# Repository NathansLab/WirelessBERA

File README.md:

# Wireless BERA

**Wireless Biopotential Electrode Recording Amplifier**

A wireless, battery-powered biopotential recording system for EEG and auditory
brainstem response (ABR/BERA) measurements.

> **BERA** stands for two things in this project:
> - **B**rainstem **E**voked **R**esponse **A**udiometry — the clinical application
> - **B**iopotential **E**lectrode **R**ecording **A**mplifier — the hardware

> **v1.0** — fabricated at Aisler, assembled, and running. Bring-up status and
> open items: [`docs/hardware_bringup_plan.md`](docs/hardware_bringup_plan.md).

---

## Repository layout

| | |
|---|---|
| [`hardware/`](hardware/) | KiCad 10 project, symbol/footprint library, LTspice simulations, fabrication outputs |
| [`firmware/wireless_bera/`](firmware/wireless_bera/) | ESP-IDF firmware for the ESP32-S3 |
| [`docs/`](docs/) | bring-up status, codec register reference, power architecture, assembly photos |
| [`measurements/`](measurements/) | raw recordings (ECG/DRL, first ABR) and the Python recording/analysis tools |
| [`report/`](report/) | Forschungspraxis report (LaTeX, MFE template) and its PDF |

`hardware/datasheets/` holds the vendor PDFs for every part. It is deliberately
kept out of git — the files are large and always re-downloadable — so a fresh
clone will not have it.

---

## Hardware

**MCU:** ESP32-S3-WROOM-1-N16R8 — Wi-Fi 802.11 b/g/n + Bluetooth 5.0 LE,
16 MB flash, 8 MB octal PSRAM.

**Analog front end**

- **LTC6373** programmable-gain instrumentation amplifier (0.25× … 16×)
- **TAC5212** 24-bit stereo codec — 2 ADC + 2 DAC channels over I²S
- **IM73A135** differential MEMS microphone for stimulus/environment monitoring
- **OPA376** driven-right-leg circuit for active common-mode rejection

**Signal path**

```
 electrode jack J6 ──► LTC6373 (PGIA) ──► TAC5212 IN2  ─┐
 MEMS mic MK1      ─────────────────────► TAC5212 IN1  ─┤ I²S ──► ESP32-S3 ──► Wi-Fi
 stimulus jack J11 ◄── TAC5212 OUT1P/OUT2P ─────────────┘
 DRL feedback      ◄── OPA376 ◄── input common mode
```

**Power** — see [power_architecture.pdf](docs/power_architecture.pdf):

- BQ24074 single-cell Li-Ion charger with power path
- TPS63000 buck-boost → 3.5 V system rail
- TPS65132W dual charge pump → ±5.4 V raw
- TPS7A39 dual ultra-low-noise LDO → ±5 V (instrumentation amplifier, DRL)
- TPS7A94 LDO → 3.3 V analog · TPS7A2033 LDO → 3.3 V digital
- Star topology and LC filters on all analog rails

**Peripherals:** microSD (SDMMC 4-bit), USB-C (USB 2.0 + ESD protection)

**PCB:** 4-layer, split GNDA/GNDD

### Daughterboard

[`hardware/daughterboard/`](hardware/daughterboard/) is an optional plug-in for
standalone LTC6373 evaluation at fixed gain 16. Stacking several of them
parallels the amplifier inputs and reduces equivalent input noise by √n.

---

## Firmware

The firmware lives in [`firmware/wireless_bera/`](firmware/wireless_bera/) — its
[README](firmware/wireless_bera/README.md) has the full picture, including the
HTTP/WebSocket API and the hardware quirks it has to respect.

It brings the analog front end up, streams both ADC channels to a browser over a
WebSocket, drives the DAC stimulus generator, and runs as its own access point
**and** as a client on an existing network at the same time.

```bash
source ~/esp/esp-idf/export.sh
cd firmware/wireless_bera
idf.py set-target esp32s3
idf.py build
```

Flash at **115200** baud — the ESP32-S3's native USB-CDC needs the slower rate
for the auto-reset handshake to line up with the macOS driver, and then no button
presses are required:

```bash
python3 -m esptool --chip esp32s3 -p /dev/cu.usbmodem101 -b 115200 \
  --before default_reset --after hard_reset write_flash \
  --flash_mode dio --flash_freq 80m --flash_size 16MB \
  0x0     build/bootloader/bootloader.bin \
  0x8000  build/partition_table/partition-table.bin \
  0x10000 build/wireless_bera.bin
```

*(To force bootloader mode by hand: hold BOOT (SW3), tap RESET (SW2), release BOOT.)*

On power-up the board raises the access point `WirelessBERA-XXXX`
(password `bera1234`) and serves its UI at <http://192.168.4.1>. The
USB-Serial/JTAG port carries both the log and a command line — type `help`, or
`wifi "My Network" mypassword` to join an existing 2.4 GHz network. Credentials
are stored in NVS only and never end up in this repository.

---

## Simulation

[`hardware/simulation/`](hardware/simulation/) holds the LTspice work behind the
analog design: transient, AC and noise runs, a common-mode/DRL testbench, and PWL
stimulus files with typical BERA waveforms.

---

## Manufacturing

[`hardware/manufacturing/`](hardware/manufacturing/) carries everything the v1.0
build was made from:

- `aisler/` — the Aisler 4-layer design-rule project
- `export/` — Gerbers, STEP models, schematic and PCB prints, BOM and Mouser order files
- `previews/` — fabrication previews and photographs of the assembled board

---

## Tools

- **EDA:** KiCad 10
- **Fabrication:** Aisler, 4-layer
- **Firmware:** ESP-IDF v5.2
- **Hardware audit:** [kicad-happy](https://github.com/aklofas/kicad-happy)

Nathan Scheufele

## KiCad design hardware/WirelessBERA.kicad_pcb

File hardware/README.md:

# Hardware

KiCad 10 project for the Wireless BERA v1.0 board.

## Layout

| | |
|---|---|
| `WirelessBERA.kicad_pro` | open this — the root project |
| `WirelessBERA.kicad_sch` | root sheet; the design is split into three sub-sheets |
| `MCU.kicad_sch` | ESP32-S3-WROOM-1, USB-C, microSD, buttons, status LED |
| `Analog.kicad_sch` | LTC6373 PGIA, TAC5212 codec, OPA376 DRL, MEMS microphone, jacks |
| `Power.kicad_sch` | BQ24074 charger, TPS63000, TPS65132W, TPS7A39/7A94/7A2033 |
| `WirelessBERA.kicad_pcb` | 4-layer layout, split GNDA/GNDD |
| `WirelessBERA.kicad_dru` | Aisler 4-layer design rules |
| `library/` | project symbols, footprints and 3D models |
| `daughterboard/` | separate LTC6373 evaluation board, fixed gain 16 |
| `simulation/` | LTspice work behind the analog design |
| `manufacturing/` | what v1.0 was actually built from |
| `datasheets/` | vendor PDFs — present on disk, deliberately not in git |

## Key reference designators

| | |
|---|---|
| `U7` | ESP32-S3-WROOM-1-N16R8 |
| `U10` | LTC6373 programmable-gain instrumentation amplifier |
| `U11` | TAC5212 codec, I²C address `0x50` |
| `U9` | OPA376 driven-right-leg driver |
| `U5` | TPS65132W dual charge pump, I²C address `0x3E` |
| `MK1` | IM73A135 MEMS microphone |
| `J6` | electrode jack (3.5 mm TRS): tip = DRL, ring = Electrode+, sleeve = Electrode− |
| `J11` | stimulus jack (3.5 mm TRS): tip = OUT2P, ring = OUT1P, sleeve = GNDA |
| `J4` | microSD slot · `J5` USB-C · `J1` battery (JST PH) |
| `J7`–`J10`, `J12`, `J13`, `TP1`–`TP22` | test headers and points |

The authoritative pin map as used by the firmware lives in
[`../firmware/wireless_bera/main/board.h`](../firmware/wireless_bera/main/board.h).

## Assembly state

The populated v1.0 board and what is deliberately left off it are documented in
[`../docs/hardware_bringup_plan.md`](../docs/hardware_bringup_plan.md).

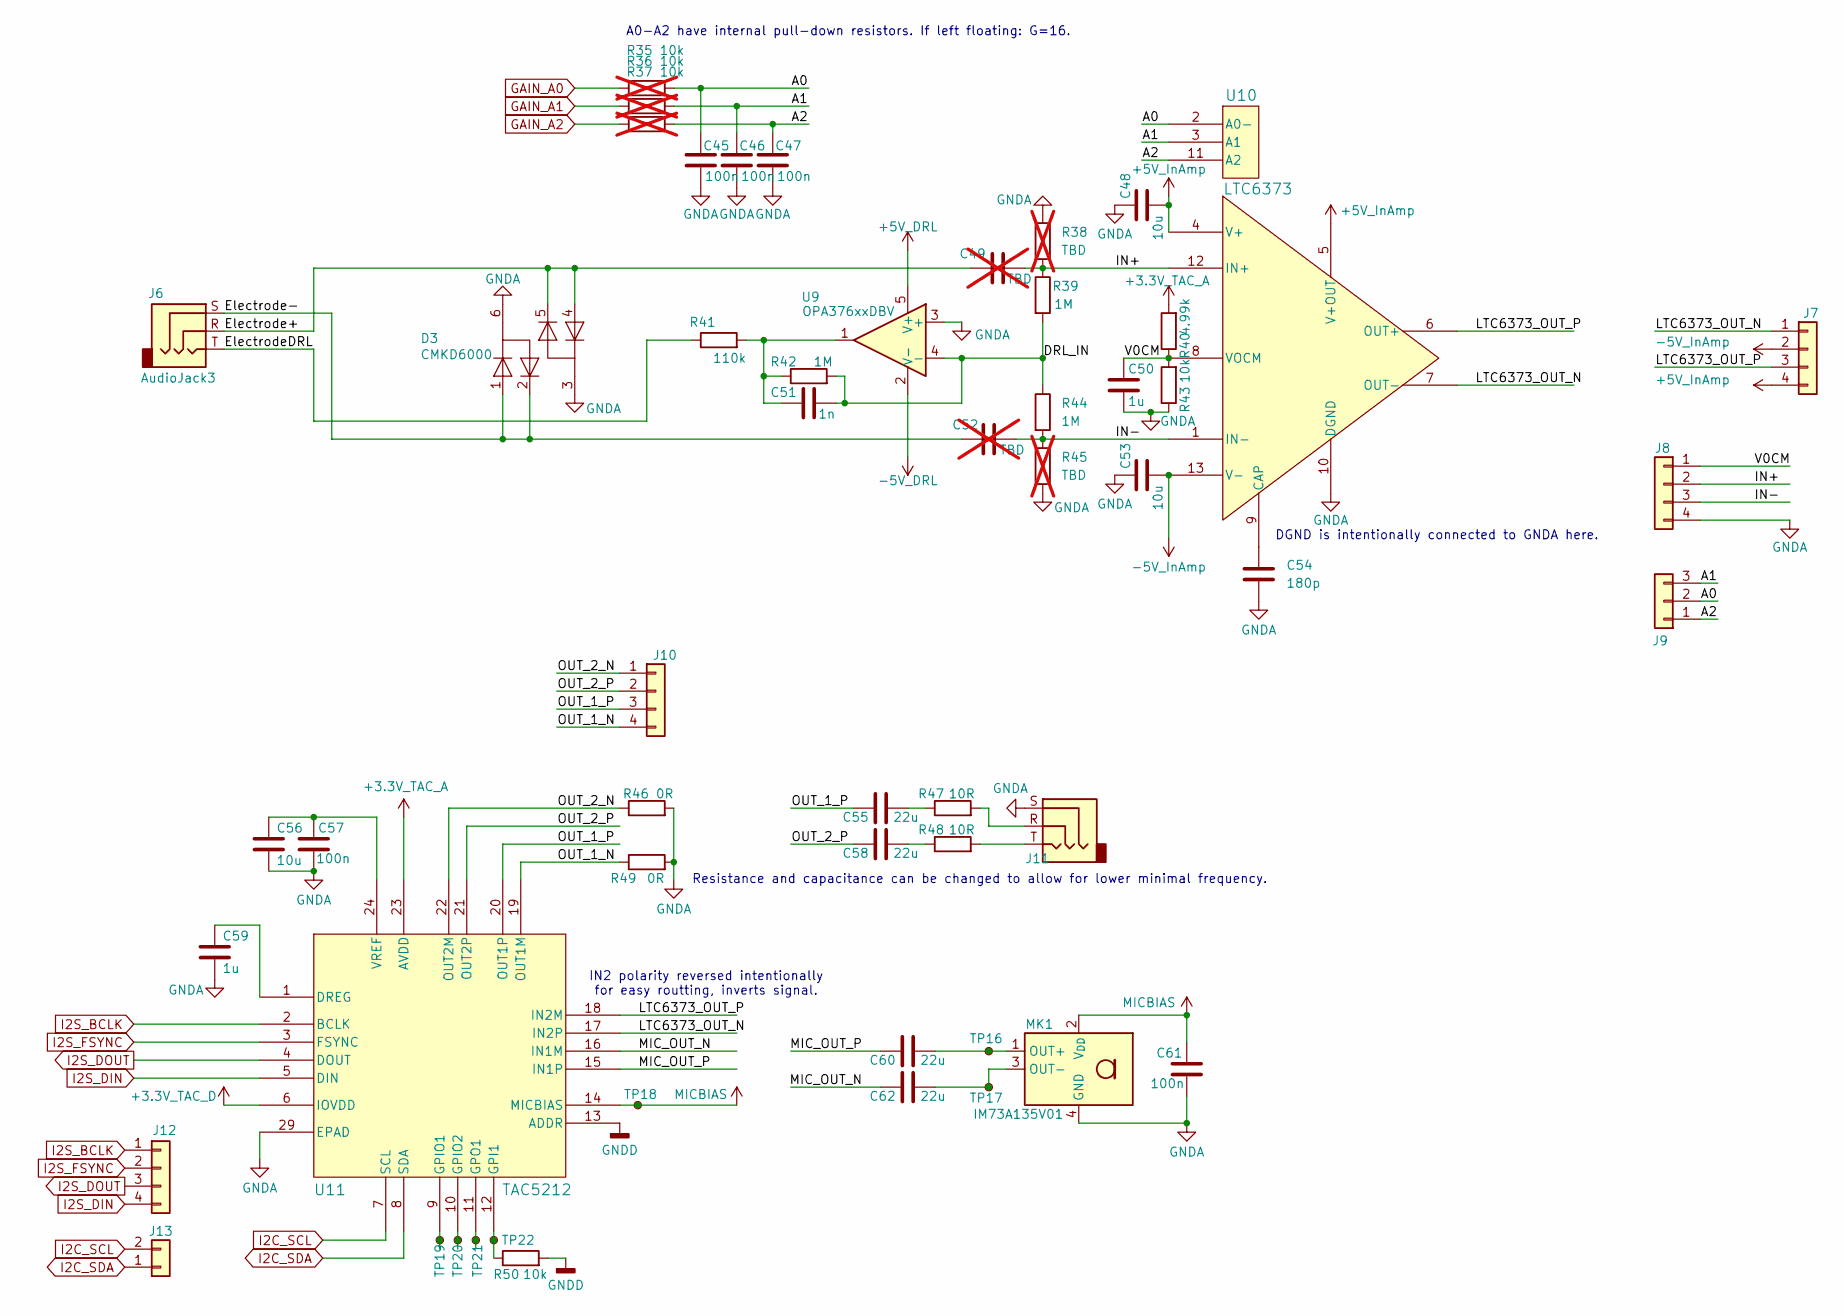
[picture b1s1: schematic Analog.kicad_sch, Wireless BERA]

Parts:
C45, C46, C47, C57, C61: 100n; C_0603_1608Metric; MPN C0603C104K5RACTU
C48, C53: 10u; C_0603_1608Metric; MPN GRM188R61C106MA73J
C49, C52: TBD; C_0603_1608Metric; not fitted
C50, C59: 1u; C_0603_1608Metric; MPN C0603C105K8PACTU
C51: 1n; C_0603_1608Metric; MPN C1608C0G1H102J080AE
C54: 180p; C_0603_1608Metric; MPN C0603C181J5GACTU
C55, C58, C60, C62: 22u; C_0805_2012Metric; MPN GRM21BR60J226ME39L
C56: 10u; C_0805_2012Metric; MPN C0805C106K4PACTU
D3: CMKD6000; SOT-363_SC-70-6; MPN CMKD6000 TR PBFREE
J6, J11: AudioJack3; Jack_3.5mm_CUI_SJ1-3523N_Horizontal; MPN SJ1-3523N
J7, J8, J10, J12: PinHeader_01x04_2.54mm_Vertical; PinHeader_1x04_P2.54mm_Vertical; MPN 61300411121
J9: PinHeader_01x03_2.54mm_Vertical; PinHeader_1x03_P2.54mm_Vertical; MPN 61300311121
J13: PinHeader_01x02_2.54mm_Vertical; PinHeader_1x02_P2.54mm_Vertical; MPN 61300211121
MK1: IM73A135V01; Infineon_PG-LLGA-5-2; MPN IM73A135V01XTSA1
R35, R36, R37: 10k; R_0603_1608Metric; MPN CRCW060310K0FKEA; not fitted
R38, R45: TBD; R_0603_1608Metric; not fitted
R39, R42, R44: 1M; R_0603_1608Metric; MPN CRCW06031M00FKEA
R40: 4.99k; R_0603_1608Metric; MPN CRCW06034K99FKEA
R41: 110k; R_0603_1608Metric; MPN CRCW0603110KFKEA
R43, R50: 10k; R_0603_1608Metric; MPN CRCW060310K0FKEA
R46, R49: 0R; R_0603_1608Metric; MPN CRCW06030000Z0EA
R47, R48: 10R; R_0603_1608Metric; MPN CRCW060310R0FKEA
TP16, TP17, TP18, TP19, TP20, TP21, TP22: TestPoint_Small; TestPoint_Pad_D1.5mm
U9: OPA376xxDBV; SOT-23-5; MPN OPA376AIDBVR
U10: LTC6373; LTC6373_DFN-12; MPN LTC6373IDFM#PBF
U11: TAC5212; TAC5212_VQFN24; MPN TAC5212IRGER

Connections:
+3.3V_TAC_A: R40.2, U11.23 (AVDD); also elsewhere on the board
+3.3V_TAC_D: U11.6 (IOVDD); also elsewhere on the board
+5V_DRL: U9.5 (V+); also elsewhere on the board
+5V_InAmp: C48.2, J7.4, U10.4 (V+), U10.5 (V+OUT); also elsewhere on the board
-5V_DRL: U9.2 (V-); also elsewhere on the board
-5V_InAmp: C53.2, J7.2, U10.13 (V-); also elsewhere on the board
/Analog/A0: C45.1, J9.2, R35.2, U10.2 (A0-)
/Analog/A1: C46.1, J9.3, R36.2, U10.3 (A1)
/Analog/A2: C47.1, J9.1, R37.2, U10.11 (A2)
/Analog/DRL_IN: C51.2, R39.2, R42.2, R44.1, U9.4 (-)
/Analog/Electrode+: C49.1, D3.4, D3.5, J6.R
/Analog/Electrode-: C52.1, D3.1, D3.2, J6.S
/Analog/ElectrodeDRL: J6.T, R41.1
/Analog/IN+: C49.2, J8.2, R38.2, R39.1, U10.12 (IN+)
/Analog/IN-: C52.2, J8.3, R44.2, R45.1, U10.1 (IN-)
/Analog/LTC6373_OUT_N: J7.1, U10.7 (OUT-), U11.17 (IN2P)
/Analog/LTC6373_OUT_P: J7.3, U10.6 (OUT+), U11.18 (IN2M)
/Analog/MIC_OUT_N: C62.1, U11.16 (IN1M)
/Analog/MIC_OUT_P: C60.1, U11.15 (IN1P)
/Analog/OUT_1_N: J10.4, R49.1, U11.19 (OUT1M)
/Analog/OUT_1_P: C55.1, J10.3, U11.20 (OUT1P)
/Analog/OUT_2_N: J10.1, R46.1, U11.22 (OUT2M)
/Analog/OUT_2_P: C58.1, J10.2, U11.21 (OUT2P)
/Analog/V0CM: C50.1, J8.1, R40.1, R43.2, U10.8 (VOCM)
GAIN_A0: R35.1; also elsewhere on the board
GAIN_A1: R36.1; also elsewhere on the board
GAIN_A2: R37.1; also elsewhere on the board
GNDA: C45.2, C46.2, C47.2, C48.1, C50.2, C53.1, C54.2, C56.2, C57.2, C59.2, C61.2, D3.3, D3.6, J8.4, J11.S, MK1.4 (GND), MK1.5 (GND), R38.1, R43.1, R45.2, R46.2, R49.2, U9.3 (+), U10.10 (DGND), U11.29 (EPAD); also elsewhere on the board
GNDD: R50.2, U11.13 (ADDR); also elsewhere on the board
I2C_SCL: J13.2, U11.7 (SCL); also elsewhere on the board
I2C_SDA: J13.1, U11.8 (SDA); also elsewhere on the board
I2S_BCLK: J12.1, U11.2 (BCLK); also elsewhere on the board
I2S_DIN: J12.4, U11.5 (DIN); also elsewhere on the board
I2S_DOUT: J12.3, U11.4 (DOUT); also elsewhere on the board
I2S_FSYNC: J12.2, U11.3 (FSYNC); also elsewhere on the board
MICBIAS: C61.1, MK1.2 (V_{DD}), TP18.1 (1_1), U11.14 (MICBIAS)
unnamed: C51.1, R41.2, R42.1, U9.1
unnamed: C55.2, R47.1
unnamed: C58.2, R48.1
unnamed: J11.R, R47.2
unnamed: J11.T, R48.2
unnamed: C60.2, MK1.1 (OUT+), TP16.1 (1_1)
unnamed: C62.2, MK1.3 (OUT-), TP17.1 (1_1)
unnamed: C54.1, U10.9 (CAP)
unnamed: C59.1, U11.1 (DREG)
unnamed: R50.1, TP22.1 (1_1), U11.12 (GPI1)
unnamed: TP19.1 (1_1), U11.9 (GPIO1)
unnamed: TP20.1 (1_1), U11.10 (GPIO2)
unnamed: TP21.1 (1_1), U11.11 (GPO1)
unnamed: C56.1, C57.1, U11.24 (VREF)

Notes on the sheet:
Resistance and capacitance can be changed to allow for lower minimal frequency.
IN2 polarity reversed intentionally for easy routting, inverts signal.
DGND is intentionally connected to GNDA here.
A0-A2 have internal pull-down resistors. If left floating: G=16.

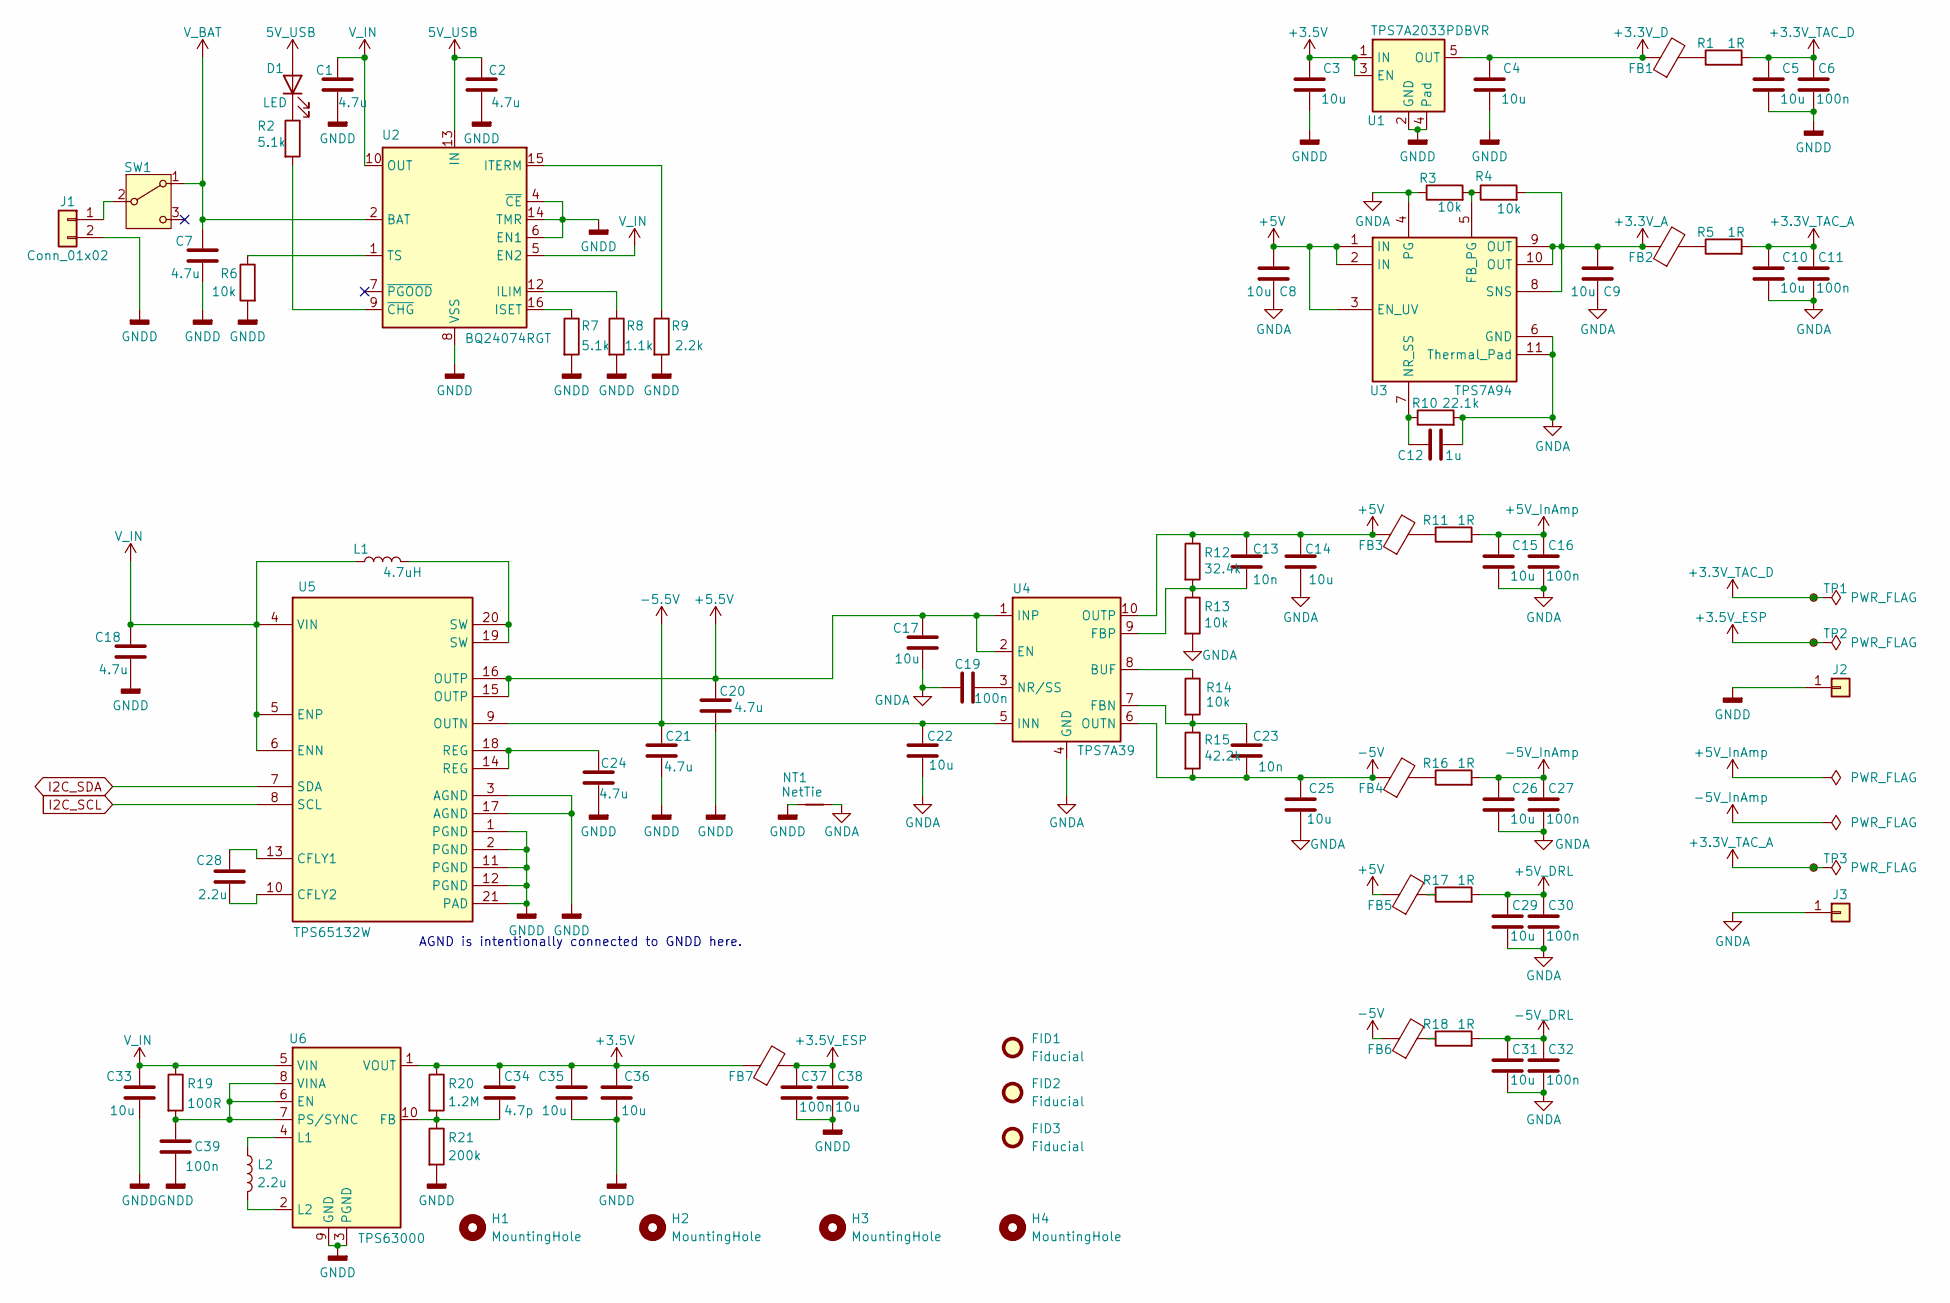
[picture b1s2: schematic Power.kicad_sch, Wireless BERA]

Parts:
C1, C2, C7, C18, C20, C21, C24: 4.7u; C_0805_2012Metric; MPN C0805C475K4PACTU
C3, C4, C5, C8, C9, C10, C14, C15, C17, C22, C25, C26, C29, C31, C33, C35, C36, C38: 10u; C_0805_2012Metric; MPN C0805C106K4PACTU
C6, C11, C16, C19, C27, C30, C32, C37, C39: 100n; C_0603_1608Metric; MPN C0603C104K5RACTU
C12: 1u; C_0603_1608Metric; MPN C0603C105K8PACTU
C13, C23: 10n; C_0603_1608Metric; MPN C0603C103G8GACTU
C28: 2.2u; C_0603_1608Metric; MPN C0603C225K8PACTU
C34: 4.7p; C_0603_1608Metric; MPN C0603C479C4HACTU
D1: LED; LED_0603_1608Metric; MPN 150060VS75000
FB1, FB2, FB3, FB4, FB5, FB6, FB7: FerriteBead; L_0805_2012Metric; MPN 742792040
FID1, FID2, FID3: Fiducial; Fiducial_0.5mm_Mask1mm
H1, H2, H3, H4: MountingHole; MountingHole_2.2mm_M2
J1: Conn_01x02; JST_PH_S2B-PH-SM4-TB_1x02-1MP_P2.00mm_Horizontal; MPN S2B-PH-SM4-TB(LF)(SN)
J2, J3: PinHeader_01x01_2.54mm_Vertical; PinHeader_1x01_P2.54mm_Vertical; MPN 61300111121
L1: 4.7uH; L_1008_2520Metric; MPN 1269AS-H-4R7M=P2
L2: 2.2u; L_0805_2012Metric; MPN LQM21PN2R2NGCD
NT1: NetTie; NetTie-2_SMD_Pad2.0mm
R1, R5, R11, R16, R17, R18: 1R; R_0603_1608Metric; MPN CRCW06031R00FKEA
R2, R7: 5.1k; R_0603_1608Metric; MPN CRCW06035K10FKEA
R3, R4, R6, R13, R14: 10k; R_0603_1608Metric; MPN CRCW060310K0FKEA
R8: 1.1k; R_0603_1608Metric; MPN CRCW06031K10FKEA
R9: 2.2k; R_0603_1608Metric; MPN CRCW06032K20FKEA
R10: 22.1k; R_0603_1608Metric; MPN CRCW060322K1FKEA
R12: 32.4k; R_0603_1608Metric; MPN CRCW060332K4FKEA
R15: 42.2k; R_0603_1608Metric; MPN CRCW060342K2FKEA
R19: 100R; R_0603_1608Metric; MPN CRCW0603100RFKEA
R20: 1.2M; R_0603_1608Metric; MPN CRCW06031M20FKEA
R21: 200k; R_0603_1608Metric; MPN CRCW0603200KFKEA
SW1: SW_SPDT; SW_SPDT_CK_JS102011SAQN; MPN JS102011SAQN
TP1, TP2, TP3: TestPoint_Small; TestPoint_Pad_D1.5mm
U1: TPS7A2033PDBVR; SOT-23-5; MPN TPS7A2033PDBVR
U2: BQ24074RGT; VQFN-16-1EP_3x3mm_P0.5mm_EP1.6x1.6mm; MPN BQ24074RGTR
U3: TPS7A94; TPS7A94_WSON-10; MPN TPS7A9401DSCR
U4: TPS7A39; Texas_S-PVSON-N10_ThermalVias; MPN TPS7A3901DSCR
U5: TPS65132W; TPS65132W_WQFN-20-TI; MPN TPS65132WRVCR
U6: TPS63000; Texas_DRC0010J_ThermalVias; MPN TPS63000DRCR

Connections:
5V_USB: C2.1, D1.2 (A), U2.13 (IN); also elsewhere on the board
+3.3V_A: C9.2, FB2.1, R4.2, U3.8 (SNS), U3.9 (OUT), U3.10 (OUT)
+3.3V_D: C4.1, FB1.1, U1.5 (OUT)
+3.3V_TAC_A: C10.1, C11.1, R5.2, TP3.1 (1_1); also elsewhere on the board
+3.3V_TAC_D: C5.1, C6.1, R1.2, TP1.1 (1_1); also elsewhere on the board
+3.5V: C3.1, C34.1, C35.1, C36.1, FB7.1, R20.1, U1.1 (IN), U1.3 (EN), U6.1 (VOUT)
+3.5V_ESP: C37.1, C38.1, FB7.2, TP2.1 (1_1); also elsewhere on the board
+5.5V: C17.1, C20.1, U4.1 (INP), U4.2 (EN), U5.15 (OUTP), U5.16 (OUTP)
+5V: C8.2, C13.1, C14.1, FB3.1, FB5.1, R12.1, U3.1 (IN), U3.2 (IN), U3.3 (EN_UV), U4.10 (OUTP)
+5V_DRL: C29.1, C30.1, R17.2; also elsewhere on the board
+5V_InAmp: C15.1, C16.1, R11.2; also elsewhere on the board
-5.5V: C21.1, C22.1, U4.5 (INN), U5.9 (OUTN)
-5V: C23.2, C25.1, FB4.1, FB6.1, R15.2, U4.6 (OUTN)
-5V_DRL: C31.1, C32.1, R18.2; also elsewhere on the board
-5V_InAmp: C26.1, C27.1, R16.2; also elsewhere on the board
GNDA: C8.1, C9.1, C10.2, C11.2, C12.2, C14.2, C15.2, C16.2, C17.2, C19.1, C22.2, C25.2, C26.2, C27.2, C29.2, C30.2, C31.2, C32.2, J3.1 (Pin_1_1), NT1.2, R3.1, R10.2, R13.2, U3.4 (PG), U3.6 (GND), U3.11 (Thermal_Pad), U4.4 (GND), U4.11 (GND); also elsewhere on the board
GNDD: C1.2, C2.2, C3.2, C4.2, C5.2, C6.2, C7.2, C18.2, C20.2, C21.2, C24.2, C33.2, C35.2, C36.2, C37.2, C38.2, C39.2, J1.2, J2.1 (Pin_1_1), NT1.1, R6.2, R7.2, R8.2, R9.2, R21.2, U1.2 (GND), U1.4 (Pad), U2.4 (~CE), U2.6 (EN1), U2.8 (VSS), U2.14 (TMR), U2.17 (VSS), U5.1 (PGND), U5.2 (PGND), U5.3 (AGND), U5.11 (PGND), U5.12 (PGND), U5.17 (AGND), U5.21 (PAD), U6.3 (PGND), U6.9 (GND), U6.11 (PGND); also elsewhere on the board
I2C_SCL: U5.8 (SCL); also elsewhere on the board
I2C_SDA: U5.7 (SDA); also elsewhere on the board
unnamed: C24.1, U5.14 (REG), U5.18 (REG)
unnamed: D1.1 (K), R2.1
unnamed: FB1.2, R1.1
unnamed: FB2.2, R5.1
unnamed: FB3.2, R11.1
unnamed: FB4.2, R16.1
unnamed: FB5.2, R17.1
unnamed: FB6.2, R18.1
unnamed: J1.1, SW1.2 (B)
unnamed: L1.2, U5.19 (SW), U5.20 (SW)
unnamed: R8.1, U2.12 (ILIM)
unnamed: R7.1, U2.16 (ISET)
unnamed: R9.1, U2.15 (ITERM)
unnamed: R6.1, U2.1 (TS)
unnamed: R2.2, U2.9 (~CHG)
unnamed: R3.2, R4.1, U3.5 (FB_PG)
unnamed: C12.1, R10.1, U3.7 (NR_SS)
unnamed: R14.1, U4.8 (BUF)
unnamed: C23.1, R14.2, R15.1, U4.7 (FBN)
unnamed: C13.2, R12.2, R13.1, U4.9 (FBP)
unnamed: C19.2, U4.3 (NR/SS)
unnamed: C28.1, U5.13 (CFLY1)
unnamed: C28.2, U5.10 (CFLY2)
unnamed: C39.1, R19.2, U6.6 (EN), U6.7 (PS/SYNC), U6.8 (VINA)
unnamed: C34.2, R20.2, R21.1, U6.10 (FB)
unnamed: L2.1, U6.4 (L1)
unnamed: L2.2, U6.2 (L2)
V_BAT: C7.1, SW1.1 (A), U2.2 (BAT), U2.3 (BAT); also elsewhere on the board
V_IN: C1.1, C18.1, C33.1, L1.1, R19.1, U2.5 (EN2), U2.10 (OUT), U2.11 (OUT), U5.4 (VIN), U5.5 (ENP), U5.6 (ENN), U6.5 (VIN)

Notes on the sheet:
AGND is intentionally connected to GNDD here.

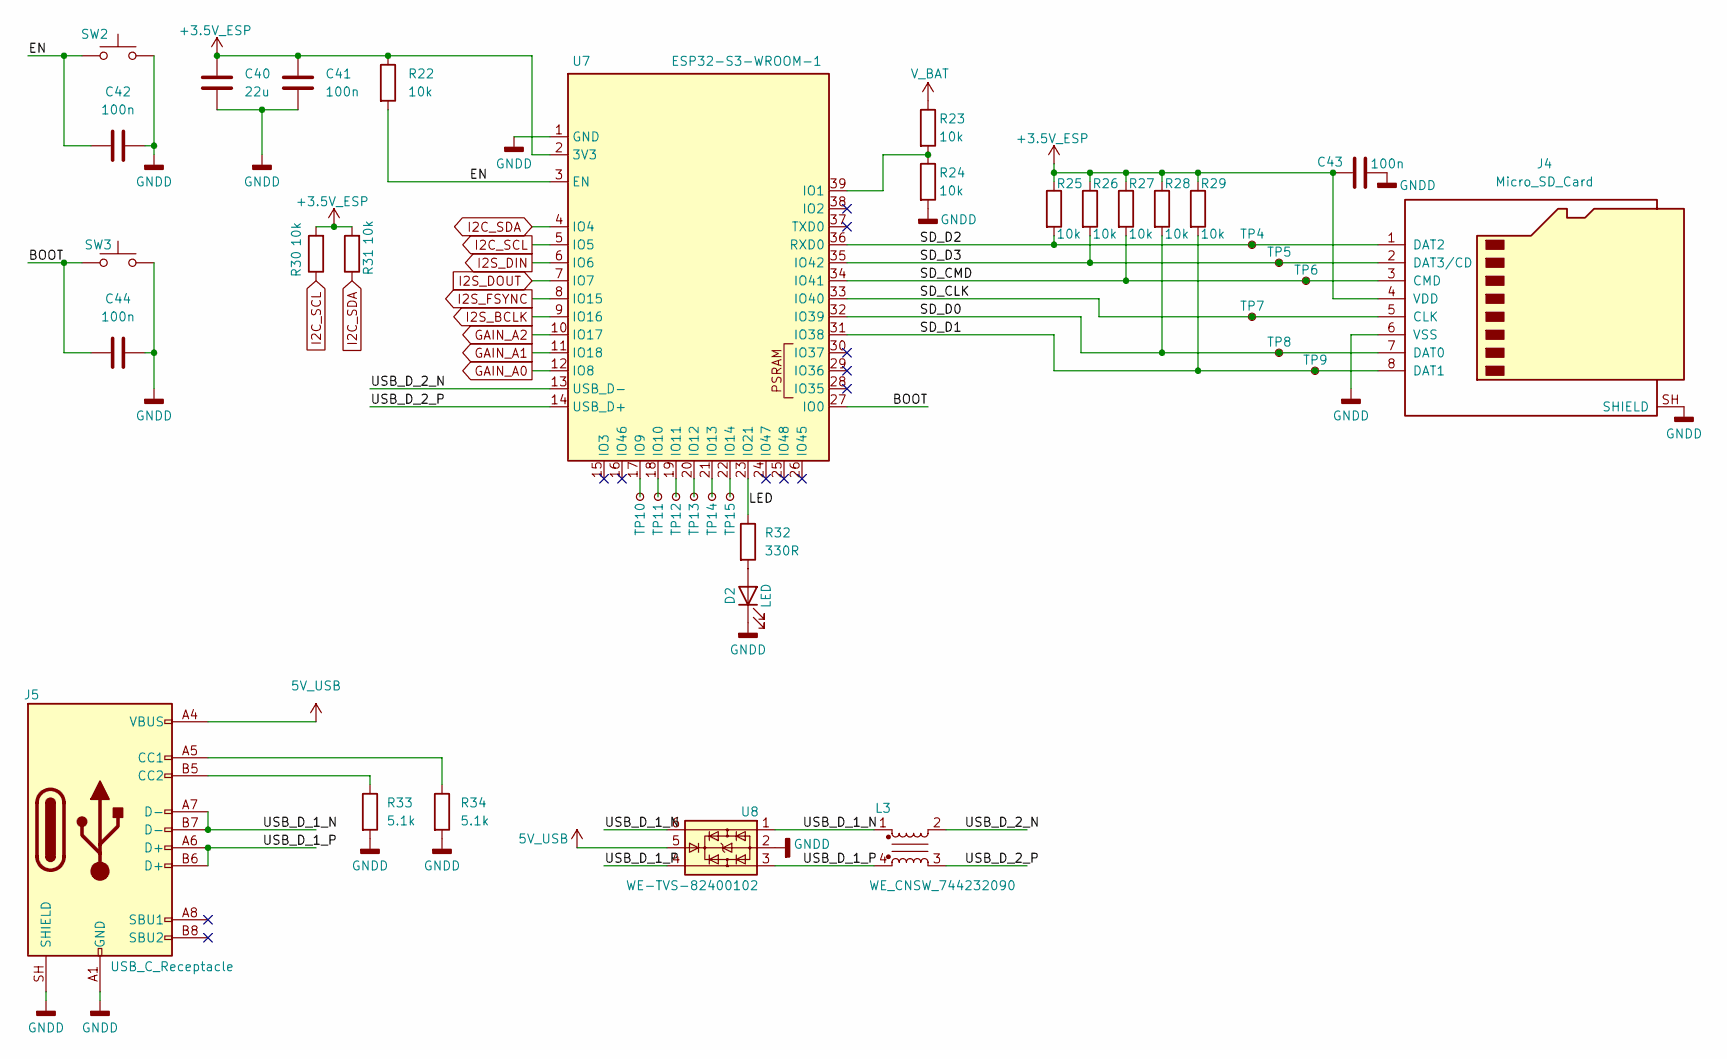
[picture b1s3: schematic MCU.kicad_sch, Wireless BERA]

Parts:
C40: 22u; C_0805_2012Metric; MPN GRM21BR60J226ME39L
C41, C42, C43, C44: 100n; C_0603_1608Metric; MPN C0603C104K5RACTU
D2: LED; LED_0603_1608Metric; MPN 150060VS75000
J4: Micro_SD_Card; microSD_HC_Wuerth_693072010801; MPN 693072010801
J5: USB_C_Receptacle; USB_C_Receptacle_GCT_USB4105-xx-A_16P_TopMnt_Horizontal; MPN 629722000214
L3: WE_CNSW_744232090; L_CommonMode_Wurth_WE-CNSW-1206; MPN 744232090
R22, R23, R24, R25, R26, R27, R28, R29, R30, R31: 10k; R_0603_1608Metric; MPN CRCW060310K0FKEA
R32: 330R; R_0603_1608Metric; MPN CRCW0603330RFKEA
R33, R34: 5.1k; R_0603_1608Metric; MPN CRCW06035K10FKEA
SW2, SW3: SW_Push; SW_SPST_EVQP2_MiddlePushTravel_H2.5mm; MPN EVQ-P2P02M
TP4, TP5, TP6, TP7, TP8, TP9, TP10, TP11, TP12, TP13, TP14, TP15: TestPoint_Small; TestPoint_Pad_D1.5mm
U7: ESP32-S3-WROOM-1; MPN ESP32-S3-WROOM-1-N16R8
U8: WE-TVS-82400102; SOT-23-6; MPN 82400102

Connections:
5V_USB: J5.A4 (VBUS), J5.A9 (VBUS), J5.B4 (VBUS), J5.B9 (VBUS), U8.5; also elsewhere on the board
+3.5V_ESP: C40.1, C41.1, C43.1, J4.4 (VDD), R22.1, R25.1, R26.1, R27.1, R28.1, R29.1, R30.2, R31.2, U7.2 (3V3); also elsewhere on the board
/MCU/BOOT: C44.1, SW3.1, U7.27 (IO0)
/MCU/EN: C42.1, R22.2, SW2.1, U7.3 (EN)
/MCU/LED: R32.1, U7.23 (IO21)
/MCU/SD_CLK: J4.5 (CLK), TP7.1 (1_1), U7.33 (IO40)
/MCU/SD_CMD: J4.3 (CMD), R27.2, TP6.1 (1_1), U7.34 (IO41)
/MCU/SD_D0: J4.7 (DAT0), R28.2, TP8.1 (1_1), U7.32 (IO39)
/MCU/SD_D1: J4.8 (DAT1), R29.2, TP9.1 (1_1), U7.31 (IO38)
/MCU/SD_D2: J4.1 (DAT2), R25.2, TP4.1 (1_1), U7.36 (RXD0)
/MCU/SD_D3: J4.2 (DAT3/CD), R26.2, TP5.1 (1_1), U7.35 (IO42)
/MCU/USB_D_1_N: J5.A7 (D-), J5.B7 (D-), L3.1, U8.1, U8.6
/MCU/USB_D_1_P: J5.A6 (D+), J5.B6 (D+), L3.4, U8.3, U8.4
/MCU/USB_D_2_N: L3.2, U7.13 (USB_D-)
/MCU/USB_D_2_P: L3.3, U7.14 (USB_D+)
GAIN_A0: U7.12 (IO8); also elsewhere on the board
GAIN_A1: U7.11 (IO18); also elsewhere on the board
GAIN_A2: U7.10 (IO17); also elsewhere on the board
GNDD: C40.2, C41.2, C42.2, C43.2, C44.2, D2.1 (K), J4.6 (VSS), J4.SH (SHIELD), J5.A1 (GND), J5.A12 (GND), J5.B1 (GND), J5.B12 (GND), J5.SH (SHIELD), R24.2, R33.2, R34.2, SW2.2, SW3.2, U7.1 (GND), U7.40 (GND), U7.41 (GND), U8.2; also elsewhere on the board
I2C_SCL: R30.1, U7.5 (IO5); also elsewhere on the board
I2C_SDA: R31.1, U7.4 (IO4); also elsewhere on the board
I2S_BCLK: U7.9 (IO16); also elsewhere on the board
I2S_DIN: U7.6 (IO6); also elsewhere on the board
I2S_DOUT: U7.7 (IO7); also elsewhere on the board
I2S_FSYNC: U7.8 (IO15); also elsewhere on the board
unnamed: D2.2 (A), R32.2
unnamed: J5.A5 (CC1), R34.1
unnamed: J5.B5 (CC2), R33.1
unnamed: R23.2, R24.1, U7.39 (IO1)
unnamed: TP10.1 (1_1), U7.17 (IO9)
unnamed: TP11.1 (1_1), U7.18 (IO10)
unnamed: TP12.1 (1_1), U7.19 (IO11)
unnamed: TP13.1 (1_1), U7.20 (IO12)
unnamed: TP14.1 (1_1), U7.21 (IO13)
unnamed: TP15.1 (1_1), U7.22 (IO14)
V_BAT: R23.1; also elsewhere on the board

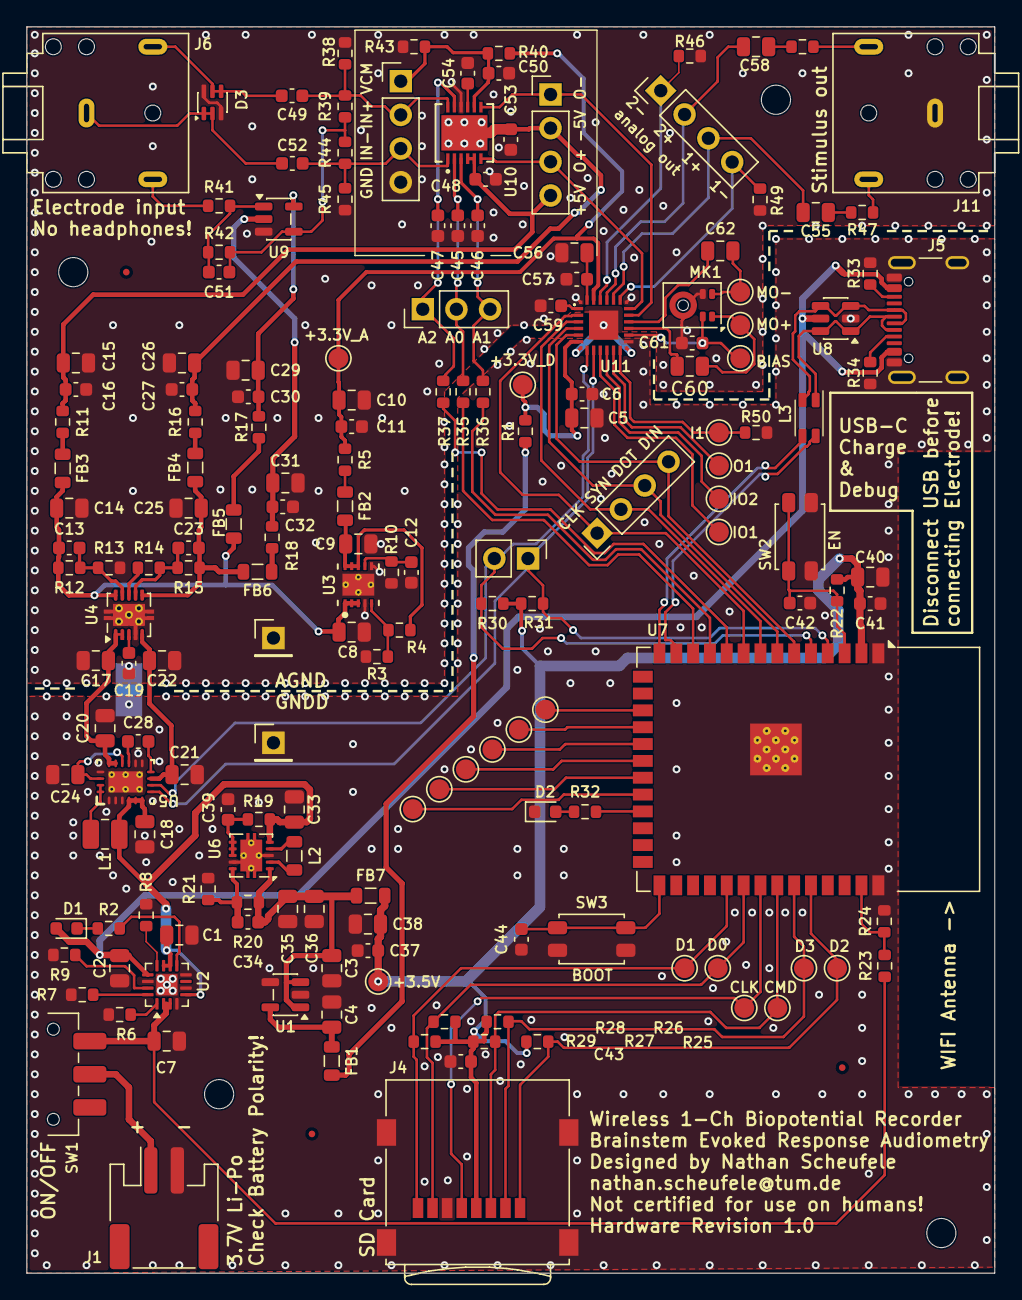
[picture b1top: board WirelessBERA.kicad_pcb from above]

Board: 4 copper layers, 73.0 x 94.0 mm, 183 parts (1 on the bottom side), 111 nets.

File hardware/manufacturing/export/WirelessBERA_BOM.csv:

"Reference","Qty","Value","Footprint","MPN","Manufacturer","Chosen_Distributor","Datasheet","Validated","DNP","Notes"
"C1,C2,C7,C18,C20,C21,C24","7","4.7u","Capacitor_SMD:C_0805_2012Metric","C0805C475K4PACTU","","","","","",""
"C3-C5,C8-C10,C14,C15,C17,C22,C25,C26,C29,C31,C33,C35,C36,C38,C56","19","10u","Capacitor_SMD:C_0805_2012Metric","C0805C106K4PACTU","","","","","",""
"C6,C11,C16,C19,C27,C30,C32,C37,C39,C41-C47,C57,C61","18","100n","Capacitor_SMD:C_0603_1608Metric","C0603C104K5RACTU","","","","","",""
"C12,C50,C59","3","1u","Capacitor_SMD:C_0603_1608Metric","C0603C105K8PACTU","","","","","",""
"C13,C23","2","10n","Capacitor_SMD:C_0603_1608Metric","C0603C103G8GACTU","","","","","",""
"C28","1","2.2u","Capacitor_SMD:C_0603_1608Metric","C0603C225K8PACTU","","","","","",""
"C34","1","4.7p","Capacitor_SMD:C_0603_1608Metric","C0603C479C4HACTU","","","","","",""
"C40,C55,C58,C60,C62","5","22u","Capacitor_SMD:C_0805_2012Metric","GRM21BR60J226ME39L","","","","","",""
"C48,C53","2","10u","Capacitor_SMD:C_0603_1608Metric","GRM188R61C106MA73J","","","","","",""
"C49,C52","2","TBD","Capacitor_SMD:C_0603_1608Metric","","","","","","DNP",""
"C51","1","1n","Capacitor_SMD:C_0603_1608Metric","C1608C0G1H102J080AE","","","","","",""
"C54","1","180p","Capacitor_SMD:C_0603_1608Metric","C0603C181J5GACTU","","","","","",""
"D1,D2","2","LED","LED_SMD:LED_0603_1608Metric","150060VS75000","","","","","",""
"D3","1","CMKD6000","Package_TO_SOT_SMD:SOT-363_SC-70-6","CMKD6000 TR PBFREE","","","https://www.mouser.de/datasheet/3/312/1/CMKD6000.pdf","","",""
"FB1-FB7","7","FerriteBead","Inductor_SMD:L_0805_2012Metric","742792040","","","https://www.we-online.com/en/components/products/WE-CBF#742792040","","",""
"J1","1","Conn_01x02","Connector_JST:JST_PH_S2B-PH-SM4-TB_1x02-1MP_P2.00mm_Horizontal","S2B-PH-SM4-TB(LF)(SN)","","","","","",""
"J2,J3","2","PinHeader_01x01_2.54mm_Vertical","Connector_PinHeader_2.54mm:PinHeader_1x01_P2.54mm_Vertical","61300111121","","","https://www.we-online.com/components/products/datasheet/6130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","","",""
"J4","1","Micro_SD_Card","Connector_Card:microSD_HC_Wuerth_693072010801","693072010801","","","https://www.we-online.com/components/products/datasheet/6930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","","",""
"J5","1","USB_C_Receptacle","Connector_USB:USB_C_Receptacle_GCT_USB4105-xx-A_16P_TopMnt_Horizontal","629722000214","","","https://www.usb.org/sites/default/files/documents/usb_type-c.zip","","",""
"J6,J11","2","AudioJack3","Connector_Audio:Jack_3.5mm_CUI_SJ1-3523N_Horizontal","SJ1-3523N","","","","","",""
"J7,J8,J10,J12","4","PinHeader_01x04_2.54mm_Vertical","Connector_PinHeader_2.54mm:PinHeader_1x04_P2.54mm_Vertical","61300411121","","","https://www.we-online.com/components/products/datasheet/6130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","","",""
"J9","1","PinHeader_01x03_2.54mm_Vertical","Connector_PinHeader_2.54mm:PinHeader_1x03_P2.54mm_Vertical","61300311121","","","https://www.we-online.com/components/products/datasheet/6130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","","",""
"J13","1","PinHeader_01x02_2.54mm_Vertical","Connector_PinHeader_2.54mm:PinHeader_1x02_P2.54mm_Vertical","61300211121","","","https://www.we-online.com/components/products/datasheet/6130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","","",""
"L1","1","4.7uH","Inductor_SMD:L_1008_2520Metric","1269AS-H-4R7M=P2","","","https://www.murata.com/en-us/products/productdata/8801124458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","","",""
"L2","1","2.2u","Inductor_SMD:L_0805_2012Metric","LQM21PN2R2NGCD","","","https://www.murata.com/en-us/products/productdata/8801124458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","","",""
"L3","1","WE_CNSW_744232090","Inductor_SMD:L_CommonMode_Wurth_WE-CNSW-1206","744232090","","","https://www.we-online.com/components/products/datasheet/7442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","","",""
"MK1","1","IM73A135V01","Sensor_Audio:Infineon_PG-LLGA-5-2","IM73A135V01XTSA1","","","https://www.infineon.com/dgdl/Infineon-IM73A135-DataSheet-v0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","","",""
"R1,R5,R11,R16-R18","6","1R","Resistor_SMD:R_0603_1608Metric","CRCW06031R00FKEA","","","","","",""
"R2,R7,R33,R34","4","5.1k","Resistor_SMD:R_0603_1608Metric","CRCW06035K10FKEA","","","","","",""
"R3,R4,R6,R13,R14,R22-R31,R43,R50","17","10k","Resistor_SMD:R_0603_1608Metric","CRCW060310K0FKEA","","","","","",""
"R8","1","1.1k","Resistor_SMD:R_0603_1608Metric","CRCW06031K10FKEA","","","","","",""
"R9","1","2.2k","Resistor_SMD:R_0603_1608Metric","CRCW06032K20FKEA","","","","","",""
"R10","1","22.1k","Resistor_SMD:R_0603_1608Metric","CRCW060322K1FKEA","","","","","",""
"R12","1","32.4k","Resistor_SMD:R_0603_1608Metric","CRCW060332K4FKEA","","","","","",""
"R15","1","42.2k","Resistor_SMD:R_0603_1608Metric","CRCW060342K2FKEA","","","","","",""
"R19","1","100R","Resistor_SMD:R_0603_1608Metric","CRCW0603100RFKEA","","","","","",""
"R20","1","1.2M","Resistor_SMD:R_0603_1608Metric","CRCW06031M20FKEA","","","","","",""
"R21","1","200k","Resistor_SMD:R_0603_1608Metric","CRCW0603200KFKEA","","","","","",""
"R32","1","330R","Resistor_SMD:R_0603_1608Metric","CRCW0603330RFKEA","","","","","",""
"R35-R37","3","10k","Resistor_SMD:R_0603_1608Metric","CRCW060310K0FKEA","","","","","DNP",""
"R38,R45","2","TBD","Resistor_SMD:R_0603_1608Metric","","","","","","DNP",""
"R39,R42,R44","3","1M","Resistor_SMD:R_0603_1608Metric","CRCW06031M00FKEA","","","","","",""
"R40","1","4.99k","Resistor_SMD:R_0603_1608Metric","CRCW06034K99FKEA","","","","","",""
"R41","1","110k","Resistor_SMD:R_0603_1608Metric","CRCW0603110KFKEA","","","","","",""
"R46,R49","2","0R","Resistor_SMD:R_0603_1608Metric","CRCW06030000Z0EA","","","","","",""
"R47,R48","2","10R","Resistor_SMD:R_0603_1608Metric","CRCW060310R0FKEA","","","","","",""
"SW1","1","SW_SPDT","Button_Switch_SMD:SW_SPDT_CK_JS102011SAQN","JS102011SAQN","","","https://www.ckswitches.com/media/1422/js.pdf","","",""
"SW2,SW3","2","SW_Push","Button_Switch_SMD:SW_SPST_EVQP2_MiddlePushTravel_H2.5mm","EVQ-P2P02M","","","https://4donline.ihs.com/images/VipMasterIC/IC/PANA/PANAS386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","","",""
"U1","1","TPS7A2033PDBVR","Package_TO_SOT_SMD:SOT-23-5","TPS7A2033PDBVR","","","https://www.ti.com/lit/ds/symlink/tps7a20.pdf","","",""
"U2","1","BQ24074RGT","Package_DFN_QFN:VQFN-16-1EP_3x3mm_P0.5mm_EP1.6x1.6mm","BQ24074RGTR","","","http://www.ti.com/lit/ds/symlink/bq24074.pdf","","",""
"U3","1","TPS7A94","BERA Project Specific Footprints:TPS7A94_WSON-10","TPS7A9401DSCR","","","https://www.ti.com/lit/ds/symlink/tps7a94.pdf","","",""
"U4","1","TPS7A39","Package_SON:Texas_S-PVSON-N10_ThermalVias","TPS7A3901DSCR","","","https://www.ti.com/lit/ds/symlink/tps7a39.pdf","","",""
"U5","1","TPS65132W","BERA Project Specific Footprints:TPS65132W_WQFN-20-TI","TPS65132WRVCR","","","https://www.ti.com/lit/gpn/tps65132","","",""
"U6","1","TPS63000","Package_SON:Texas_DRC0010J_ThermalVias","TPS63000DRCR","","","http://www.ti.com/lit/ds/symlink/tps63000.pdf","","",""
"U7","1","ESP32-S3-WROOM-1","RF_Module:ESP32-S3-WROOM-1","ESP32-S3-WROOM-1-N16R8","","","https://www.espressif.com/sites/default/files/documentation/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","","",""
"U8","1","WE-TVS-82400102","Package_TO_SOT_SMD:SOT-23-6","82400102","","","https://www.we-online.com/components/products/datasheet/8240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","","",""
"U9","1","OPA376xxDBV","Package_TO_SOT_SMD:SOT-23-5","OPA376AIDBVR","","","http://www.ti.com/lit/ds/symlink/opa376.pdf","","",""
"U10","1","LTC6373","BERA Project Specific Footprints:LTC6373_DFN-12","LTC6373IDFM#PBF","","","https://www.analog.com/media/en/technical-documentation/data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","","",""
"U11","1","TAC5212","BERA Project Specific Footprints:TAC5212_VQFN24","TAC5212IRGER","","","https://www.ti.com/lit/gpn/tac5212","","",""
